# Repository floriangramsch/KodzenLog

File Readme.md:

docker build --platform linux/amd64 -t cats.floxsite.de/hv-bingerschlag .

You have to clone git@github.com:floriangramsch/FloxSite-Hub.git
Then run the docker-compose.local.yml in /FloxSite-Hub/KodzenLog

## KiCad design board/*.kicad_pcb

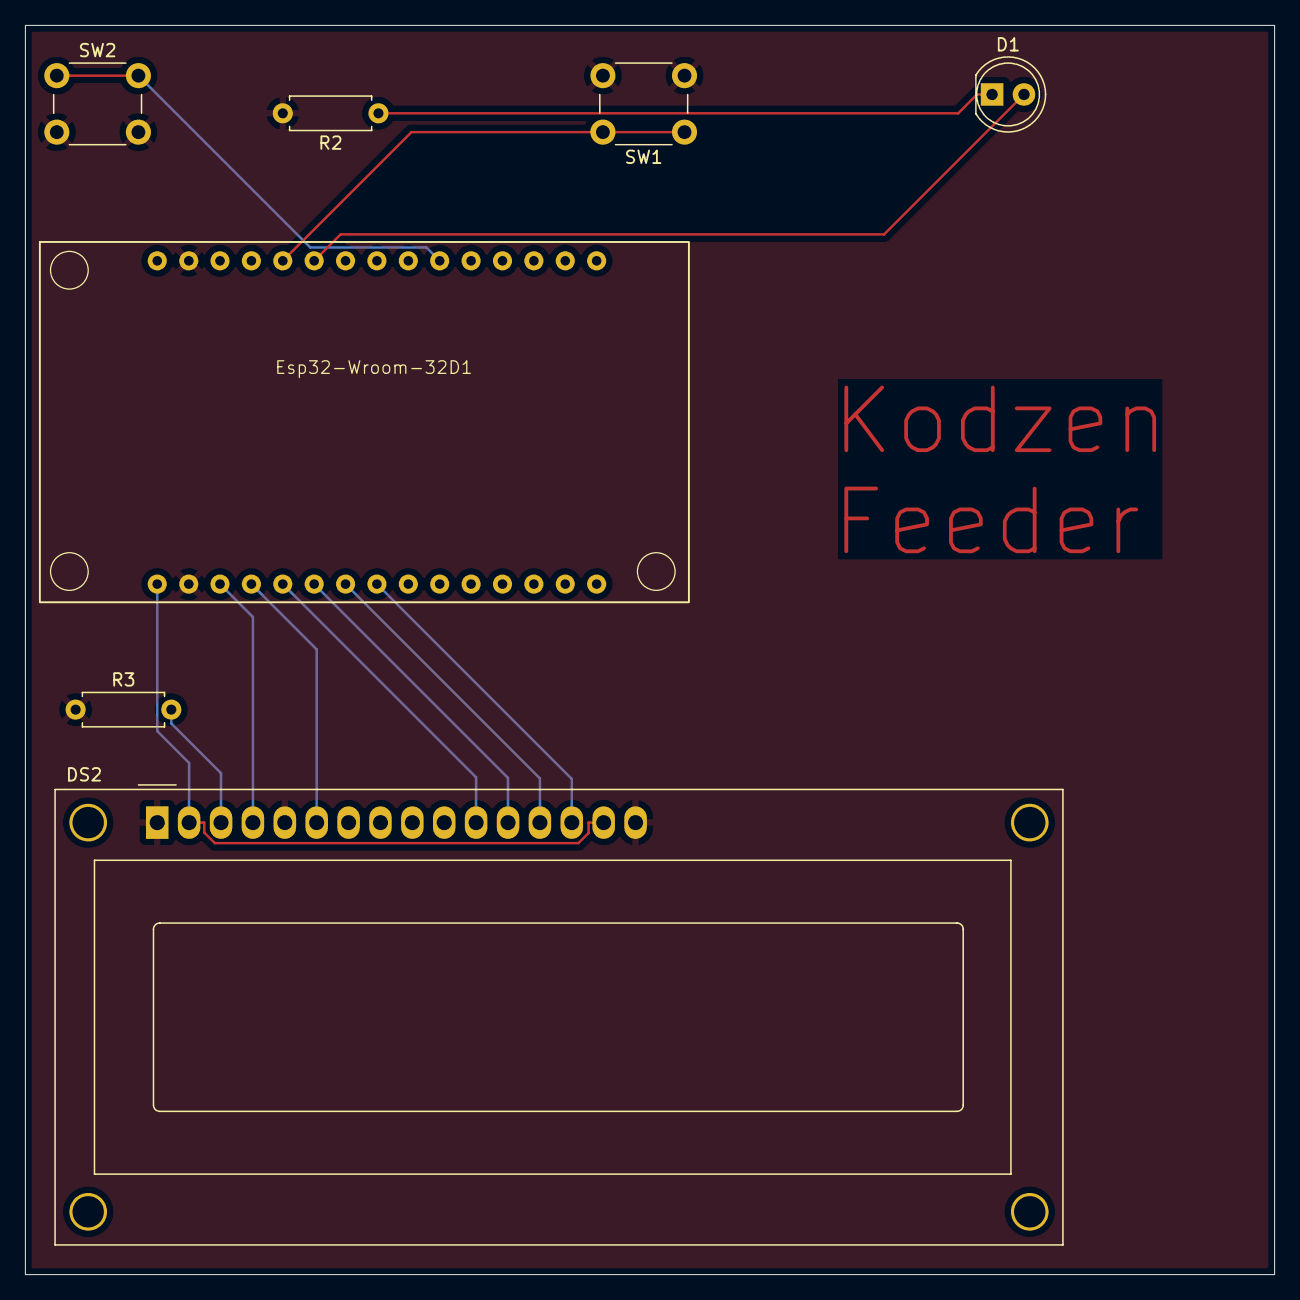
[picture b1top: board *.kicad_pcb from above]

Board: 2 copper layers, 99.5 x 99.5 mm, 7 parts (0 on the bottom side), 13 nets.

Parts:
D1: LED; LED_D5.0mm
DS2: WC1602A
Esp32-Wroom-32D1: esp32_my_footpring
R2, R3: R; R_Axial_DIN0207_L6.3mm_D2.5mm_P7.62mm_Horizontal
SW1, SW2: SW_Push; SW_PUSH_6mm_H5mm

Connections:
GND: DS2.1 (VSS), DS2.5 (R/W), DS2.16 (LED(-)), Esp32-Wroom-32D1.1 (GND), Esp32-Wroom-32D1.38 (GND), R2.2, R3.1, SW1.2, SW2.2
unnamed: D1.2 (A), Esp32-Wroom-32D1.12 (D27)
unnamed: D1.1 (K), R2.1
unnamed: DS2.11 (D4), Esp32-Wroom-32D1.26 (D4)
unnamed: DS2.12 (D5), Esp32-Wroom-32D1.27 (D16)
unnamed: DS2.13 (D6), Esp32-Wroom-32D1.28 (D17)
unnamed: DS2.14 (D7), Esp32-Wroom-32D1.29 (D5)
unnamed: DS2.6 (E), Esp32-Wroom-32D1.24 (D2)
unnamed: DS2.2 (VDD), DS2.15 (LED(+)), Esp32-Wroom-32D1.2 (3V3)
unnamed: DS2.4 (RS), Esp32-Wroom-32D1.23 (D15)
unnamed: DS2.3 (VO), R3.2
unnamed: Esp32-Wroom-32D1.13 (D14), SW1.1
unnamed: Esp32-Wroom-32D1.8 (D32), SW2.1

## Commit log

2024-11-09 moving
2024-11-09 test
2024-11-09 update project name
2024-11-09 back to normal
2024-11-15 test log
2024-11-15 readme
2025-05-30 feat: - optimised docker files - changed port - LEO... :(
2025-05-30 split dev and deploy.. thus removed docker compose and changed workflow
2025-05-30 changed registry endpoint
2025-05-30 miss you leo <3
2025-05-30 support multiplatform
2025-05-30 better workflow
2025-05-30 use of node:24-slim
2025-05-30 use of alpine
2025-07-08 feat: return time when cat is feeded
2025-07-19 feat: server send local time back
2025-08-25 feat: firmware and board
2025-08-25 feat: 3d files
